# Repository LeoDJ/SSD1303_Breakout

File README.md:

# SSD1303 Breakout Board

A breakout board for a specific SSD1303 OLED display.  
Optimized for low-cost PCB assembly services from a specific chinese manufacturer with blue logo.

You can [preview the PCB](https://kicanvas.org/?github=https%3A%2F%2Fgithub.com%2FLeoDJ%2FSSD1303_Breakout%2Fblob%2Fmain%2FSSD1303_Breakout.kicad_pcb) using the amazing KiCanvas. (Or the [schematic](https://kicanvas.org/?github=https%3A%2F%2Fgithub.com%2FLeoDJ%2FSSD1303_Breakout%2Ftree%2Fmain) if I forget to update the [PDF](./SSD1303_Breakout.pdf) ^^' )

## Pinout
| Pin | Function                                                                     |
|-----|------------------------------------------------------------------------------|
| GND | GND                                                                          |
| VCC | 3.3 - 5 V (up to ~250mA[^1])                                                 |
| CLK | SPI: `SCK` <br>I²C: `SCL`                                                    |
| DI  | SPI: `MOSI` <br>I²C: `SDA`                                                   |
| RES | Reset (active low)                                                           |
| DC  | SPI: data/command line <br>I²C: address. 0: `0x3C` / 1: `0x3D` (default low) |
| CS  | SPI: `CS`                                                                    |

* I/O pins are 5V tolerant
* To switch between SPI and I²C mode, you need to bridge / unbridge the solder jumper at the back (default is SPI)
* I've tried to make the pinout as compatible as possible to existing OLED modules, but there are many different variants

[^1]: Might draw up to ~250 mA @ 3.3V with all pixels on, guesstimated.  
I've measured roughly 50mA @ 12V with the highest brightness and all pixels on, so with pessimistic conversion losses around 750mW.

## Rev 1.0
### Issues
- In SPI mode, the "serial data out" pin of the SSD1303 (pin D2) doesn't always stay high[^2], as was initially measured. Thus the simple diode trick to allow both SPI and I²C mode, without needing to "keep D2 disconnected in SPI mode" as stated in the datasheet, won't work.
  - **Workaround**: Remove D1 (below the FPC) for working SPI mode
  - Fix in next revision: An additional FET in series to the D2 signal that gets activated by the solder jumper
- An additional solder jumper for I²C address would probably be nice
  - In case one wants to use the breakout board on a 4-pin-only socket
  - **Workaround**: solder a jumper wire from the DC pin/pad to the VCC pin/pad to select address `0x3D`

[^2]: It appears to shift out some kind of data, maybe from an internal register. The SSD1303 datasheet doesn't give any hint to the behaviour of pin D2 in SPI mode, except to keep it disconnected.  
Over time the value that gets shifted out accumulates 1 bits. Starting at some random value with few bits set on power-up. (It probably turns into a constant high signal as soon as it reaches 0xFF, but I could only actually observe it up to 0x7F/0xF7 in my last measurement.)  
When the pin is actively pulled low by the SSD1303, it interferes through the diode D1 with the actual data meant for the data input pin D1.  

### Screenshots of 3D view
Somehow I got a bit carried away for a relatively simple design, but otoh I've learned a lot again.

<p float="left" style="display: flex; flex-wrap: wrap; align-items: center;">
  &nbsp;
  
  &nbsp;
  
</p>

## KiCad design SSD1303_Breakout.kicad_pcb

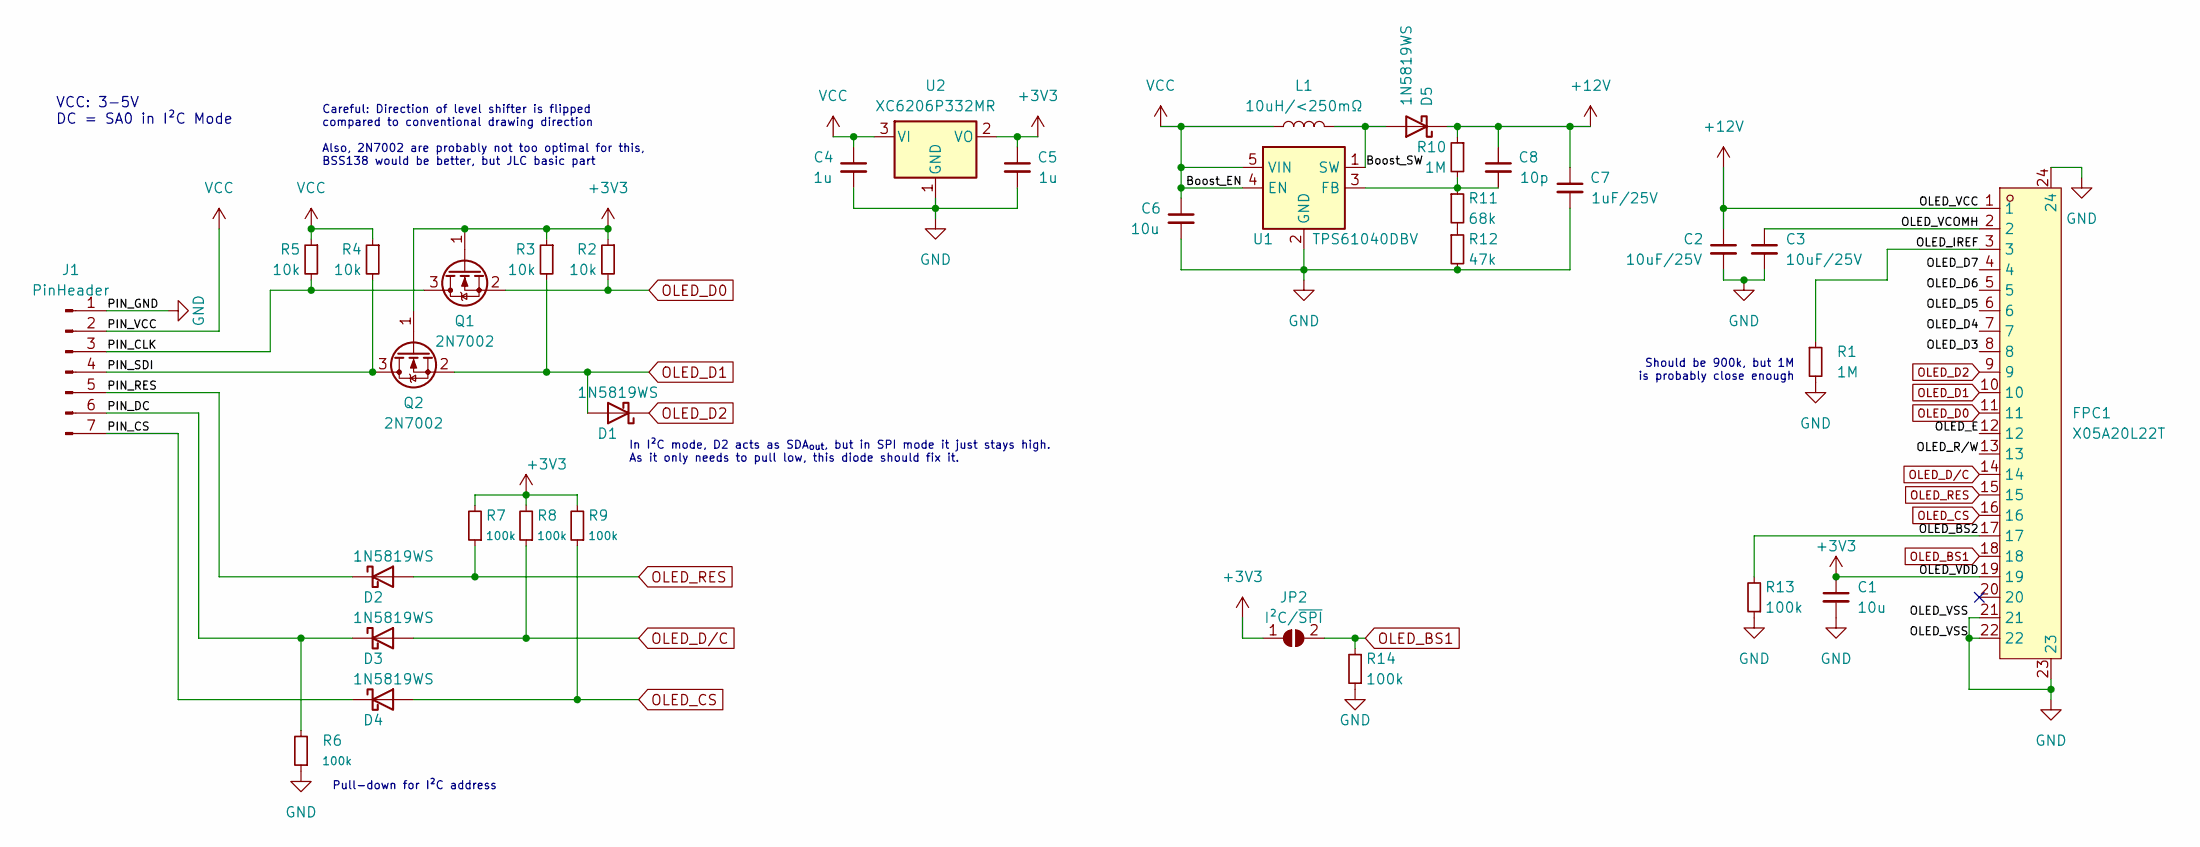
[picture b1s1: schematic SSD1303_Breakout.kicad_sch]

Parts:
C1, C6: 10u; C_0603_1608Metric; LCSC C96446
C2, C3: 10uF/25V; C_0603_1608Metric; LCSC C96446
C4, C5: 1u; C_0402_1005Metric; LCSC C52923
C7: 1uF/25V; C_0402_1005Metric; LCSC C52923
C8: 10p; C_0402_1005Metric; LCSC C32949
D1, D2, D3, D4, D5: 1N5819WS; D_SOD-323; LCSC C191023
FPC1: X05A20L22T; FFC-SMD_22P-P0.50_X05A20L22T; LCSC Part C388675
J1: PinHeader; PinHeader_1x07_P2.54mm_Vertical
JP2: I²C/~{SPI}; SolderJumper-2_P1.3mm_Open_TrianglePad1.0x1.5mm
L1: 10uH/<250mΩ; IND-SMD_L5.0-W5.0; LCSC C963773
Q1, Q2: 2N7002; SOT-23; LCSC C8545
R1, R10: 1M; R_0402_1005Metric; LCSC C26083
R2, R3, R4, R5: 10k; R_0402_1005Metric; LCSC C25744
R6, R7, R8, R9, R13, R14: 100k; R_0402_1005Metric; LCSC C25741
R11: 68k; R_0402_1005Metric; LCSC C36871
R12: 47k; R_0402_1005Metric; LCSC C25792
U1: TPS61040DBV; SOT-23-5; LCSC C7722
U2: XC6206P332MR; SOT-23; LCSC C5446

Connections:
+3V3: C1.1, C5.1, FPC1.19, JP2.1 (A), Q1.1 (G), Q2.1 (G), R2.1, R3.1, R7.2, R8.2, R9.2, U2.2 (VO)
+12V: C2.1, C7.1, C8.1, D5.1 (K), FPC1.1, R10.1
/Boost_SW: D5.2 (A), L1.2, U1.1 (SW)
/OLED_BS2: FPC1.17, R13.2
/OLED_D3: FPC1.8
/OLED_D4: FPC1.7
/OLED_D5: FPC1.6
/OLED_D6: FPC1.5
/OLED_D7: FPC1.4
/OLED_E: FPC1.12
/OLED_IREF: FPC1.3, R1.1
/OLED_R/W: FPC1.13
/OLED_VCOMH: C3.1, FPC1.2
/PIN_CLK: J1.3, Q1.3 (D), R5.2
/PIN_CS: D4.1 (K), J1.7
/PIN_DC: D3.1 (K), J1.6, R6.2
/PIN_RES: D2.1 (K), J1.5
/PIN_SDI: J1.4, Q2.3 (D), R4.2
GND: C1.2, C2.2, C3.2, C4.2, C5.2, C6.2, C7.2, FPC1.21, FPC1.22, FPC1.23, FPC1.24, J1.1, R1.2, R6.1, R12.2, R13.1, R14.1, U1.2 (GND), U2.1 (GND)
unnamed: R11.2, R12.1
unnamed: C8.2, R10.2, R11.1, U1.3 (FB)
OLED_BS1: FPC1.18, JP2.2 (B), R14.2
OLED_CS: D4.2 (A), FPC1.16, R9.1
OLED_D0: FPC1.11, Q1.2 (S), R2.2
OLED_D1: D1.2 (A), FPC1.10, Q2.2 (S), R3.2
OLED_D2: D1.1 (K), FPC1.9
OLED_D/C: D3.2 (A), FPC1.14, R8.1
OLED_RES: D2.2 (A), FPC1.15, R7.1
VCC: C4.1, C6.1, J1.2, L1.1, R4.1, R5.1, U1.4 (EN), U1.5 (VIN), U2.3 (VI)

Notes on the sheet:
Should be 900k, but 1M is probably close enough
In I²C mode, D2 acts as SDA_{out}, but in SPI mode it just stays high. As it only needs to pull low, this diode should fix it.
Pull-down for I²C address
Careful: Direction of level shifter is flipped compared to conventional drawing direction Also, 2N7002 are probably not too optimal for this, BSS138 would be better, but JLC basic part
VCC: 3-5V DC = SA0 in I²C Mode

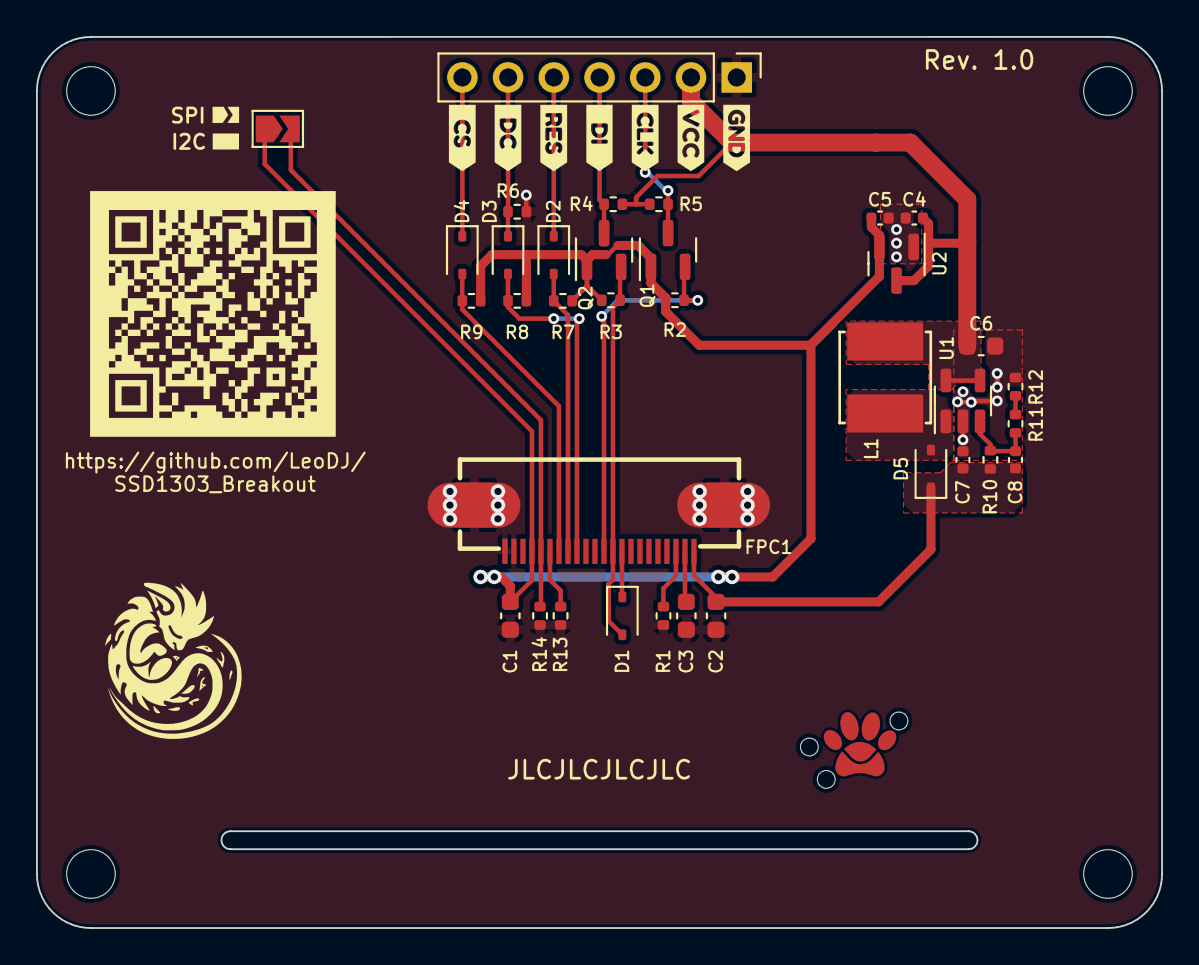
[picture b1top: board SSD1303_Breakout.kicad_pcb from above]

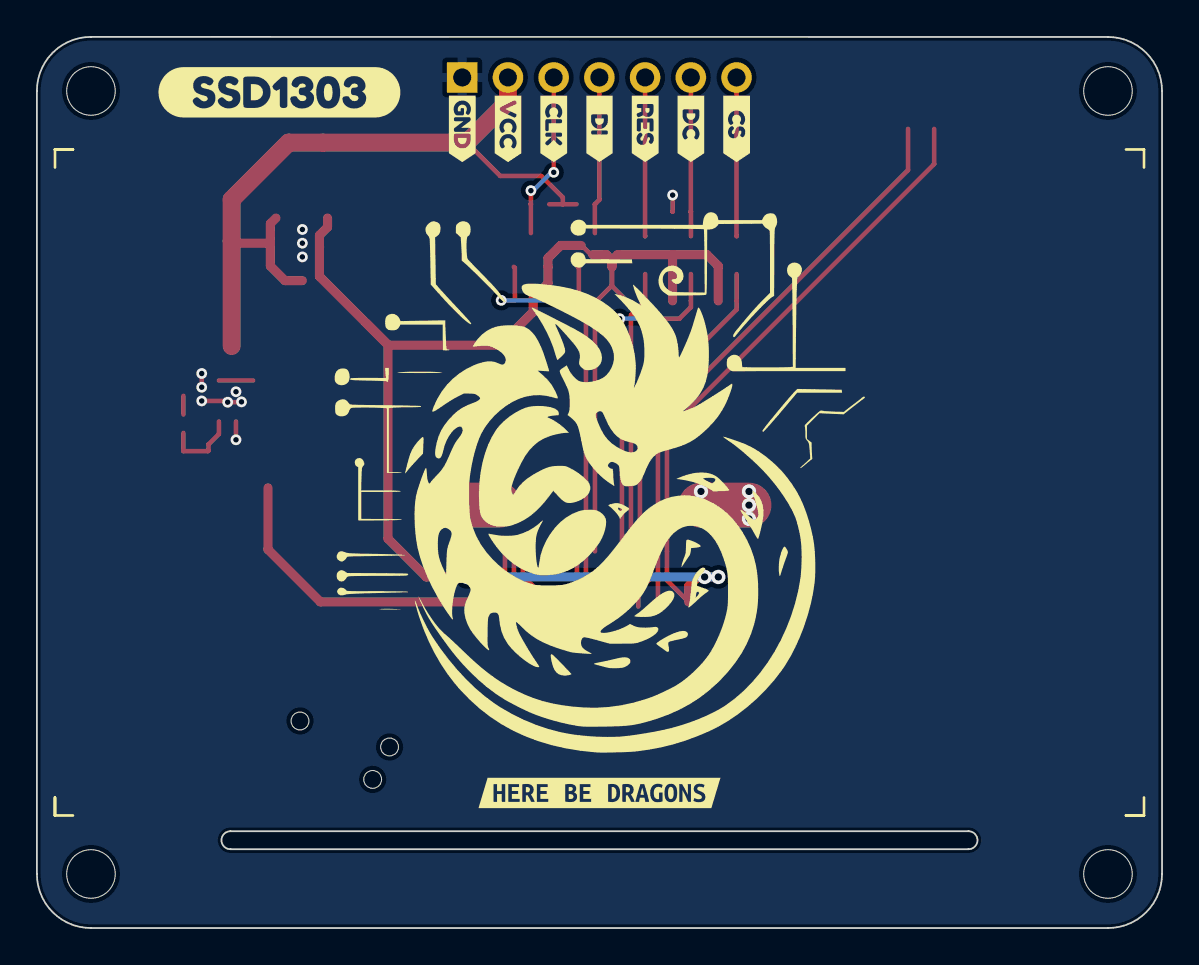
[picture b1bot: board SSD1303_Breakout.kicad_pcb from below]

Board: 2 copper layers, 62.5 x 49.5 mm, 51 parts (9 on the bottom side), 22 nets.

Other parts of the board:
kibuzzard-6492A15D: G***; kibuzzard-6492A15D
kibuzzard-649270A0, kibuzzard-649270A0#2: G***; kibuzzard-649270A0
kibuzzard-649270A6, kibuzzard-649270A6#2: G***; kibuzzard-649270A6
kibuzzard-649270AD, kibuzzard-649270AD#2: G***; kibuzzard-649270AD
kibuzzard-649270B3, kibuzzard-649270B3#2: G***; kibuzzard-649270B3
kibuzzard-649270BA, kibuzzard-649270BA#2: G***; kibuzzard-649270BA
kibuzzard-6492708E, kibuzzard-6492708E#2: G***; kibuzzard-6492708E
kibuzzard-64927098, kibuzzard-64927098#2: G***; kibuzzard-64927098
kibuzzard-64927129: G***; kibuzzard-64927129

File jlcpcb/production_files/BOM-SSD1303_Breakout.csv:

Comment,Designator,Footprint,LCSC
1N5819WS,"D1,D2,D3,D4,D5",D_SOD-323,C191023
100k,"R13,R14,R6,R7,R8,R9",R_0402_1005Metric,C25741
10k,"R2,R3,R4,R5",R_0402_1005Metric,C25744
47k,R12,R_0402_1005Metric,C25792
1M,"R1,R10",R_0402_1005Metric,C26083
10p,C8,C_0402_1005Metric,C32949
68k,R11,R_0402_1005Metric,C36871
X05A20L22T,FPC1,FFC-SMD_22P-P0.50_X05A20L22T,C388675
1u,"C4,C5,C7",C_0402_1005Metric,C52923
XC6206P332MR,U2,SOT-23,C5446
TPS61040DBV,U1,SOT-23-5,C7722
2N7002,"Q1,Q2",SOT-23,C8545
10uH/<250mΩ,L1,IND-SMD_L5.0-W5.0,C963773
10u,"C1,C2,C3,C6",C_0603_1608Metric,C96446
PinHeader,J1,PinHeader_1x07_P2.54mm_Vertical,

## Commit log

2023-06-21 mainly done, some minor touchups still todo
2023-06-21 add preliminary fabrication outputs
2023-06-22 final™ touches
2023-06-22 add pinout to README
2023-07-06 add findings from yesterdays tests of Rev 1.0
